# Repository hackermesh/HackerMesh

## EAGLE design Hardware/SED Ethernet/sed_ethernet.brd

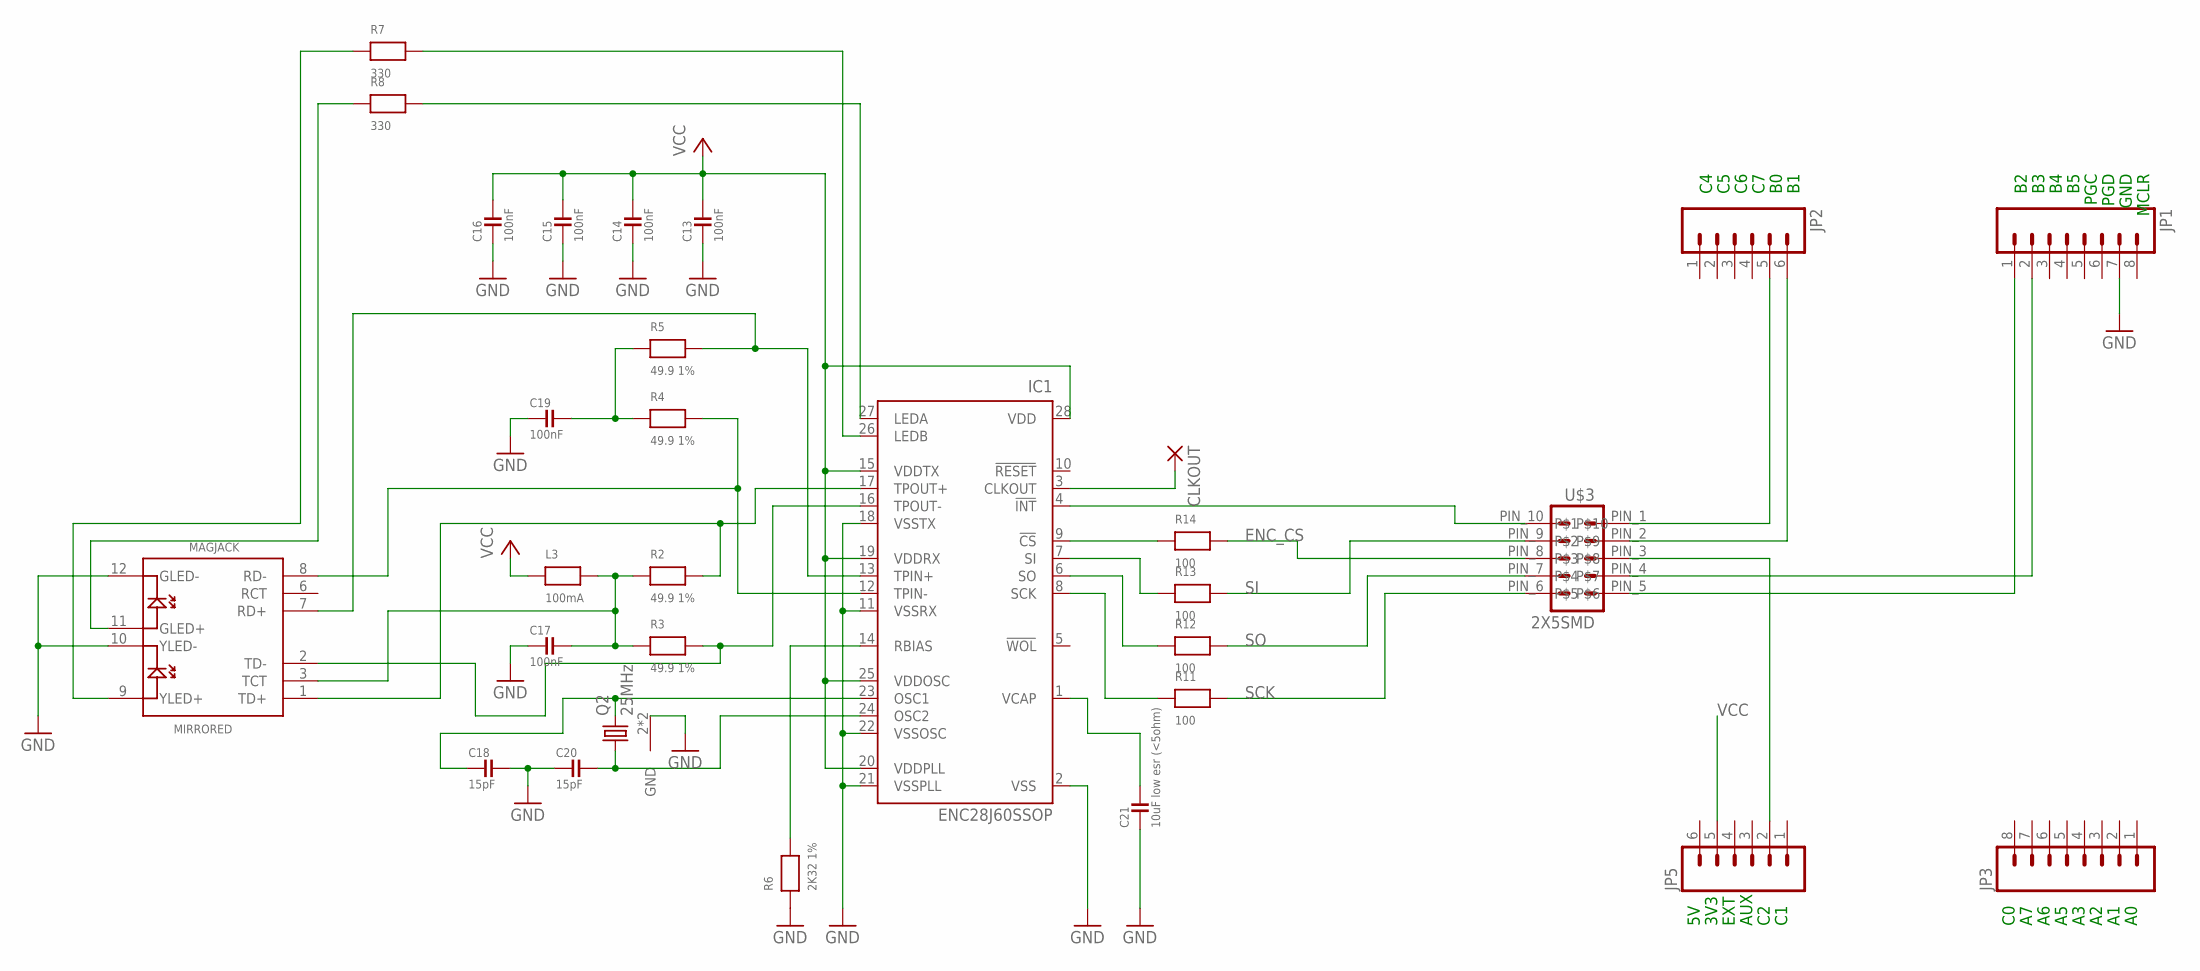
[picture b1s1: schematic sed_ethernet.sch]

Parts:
C13, C14, C15, C16, C17, C19: 100nF; 0805
C18, C20: 15pF; 0805
C21: 10uF low esr (<5ohm); 0805
CLKOUT: SMD2; SMD1,27-2,54
IC1: ENC28J60SSOP; SSOP28
JP1, JP3: M08; 1X08
JP2, JP5: M06SIP; 1X06
L3: 100mA; 0805
MIRRORED: MAGJACK
Q2: 25MHz; CRYSTAL-SMD-5X3
R2, R3, R4, R5: 49.9 1%; 0805
R6: 2K32 1%; 0805
R7, R8: 330; 0805
R11, R12, R13, R14: 100; 0805
U$3: 2X5SMD

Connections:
ENC_CS: R14.P$4 (2), U$3.PIN_8
GND: C13.P$3 (1), C14.P$3 (1), C15.P$3 (1), C16.P$3 (1), C17.P$3 (1), C18.P$4 (2), C19.P$3 (1), C20.P$3 (1), C21.P$3 (1), IC1.2 (VSS), IC1.11 (VSSRX), IC1.18 (VSSTX), IC1.21 (VSSPLL), IC1.22 (VSSOSC), JP1.7, MIRRORED.10 (YLED-), MIRRORED.12 (GLED-), Q2.2 (GND), Q2.4 (GND), R6.P$3 (1)
unnamed: IC1.14 (RBIAS), R6.P$4 (2)
unnamed: IC1.8 (SCK), R11.P$3 (1)
unnamed: IC1.6 (SO), R12.P$3 (1)
unnamed: IC1.7 (SI), R13.P$3 (1)
unnamed: IC1.9 (!CS), R14.P$3 (1)
unnamed: C21.P$4 (2), IC1.1 (VCAP)
unnamed: IC1.27 (LEDA), R8.P$4 (2)
unnamed: MIRRORED.11 (GLED+), R8.P$3 (1)
unnamed: MIRRORED.9 (YLED+), R7.P$3 (1)
unnamed: IC1.26 (LEDB), R7.P$4 (2)
unnamed: CLKOUT.1, IC1.3 (CLKOUT)
unnamed: IC1.17 (TPOUT+), MIRRORED.1 (TD+), R2.P$4 (2)
unnamed: IC1.16 (TPOUT-), MIRRORED.2 (TD-), R3.P$4 (2)
unnamed: C17.P$4 (2), L3.P$4 (2), MIRRORED.3 (TCT), R2.P$3 (1), R3.P$3 (1)
unnamed: IC1.13 (TPIN+), MIRRORED.7 (RD+), R5.P$4 (2)
unnamed: IC1.12 (TPIN-), MIRRORED.8 (RD-), R4.P$4 (2)
unnamed: C19.P$4 (2), R4.P$3 (1), R5.P$3 (1)
unnamed: C18.P$3 (1), IC1.23 (OSC1), Q2.3 (2)
unnamed: C20.P$4 (2), IC1.24 (OSC2), Q2.1
unnamed: JP2.5, U$3.PIN_1
unnamed: IC1.4 (!INT), U$3.PIN_10
unnamed: JP5.2, U$3.PIN_3
unnamed: JP2.6, U$3.PIN_2
unnamed: JP1.2, U$3.PIN_4
unnamed: JP1.1, U$3.PIN_5
SCK: R11.P$4 (2), U$3.PIN_6
SI: R13.P$4 (2), U$3.PIN_9
SO: R12.P$4 (2), U$3.PIN_7
VCC: C13.P$4 (2), C14.P$4 (2), C15.P$4 (2), C16.P$4 (2), IC1.15 (VDDTX), IC1.19 (VDDRX), IC1.20 (VDDPLL), IC1.25 (VDDOSC), IC1.28 (VDD), JP5.5, L3.P$3 (1)

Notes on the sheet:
3V3
EXT
AUX
PGC
PGD
GND
MCLR

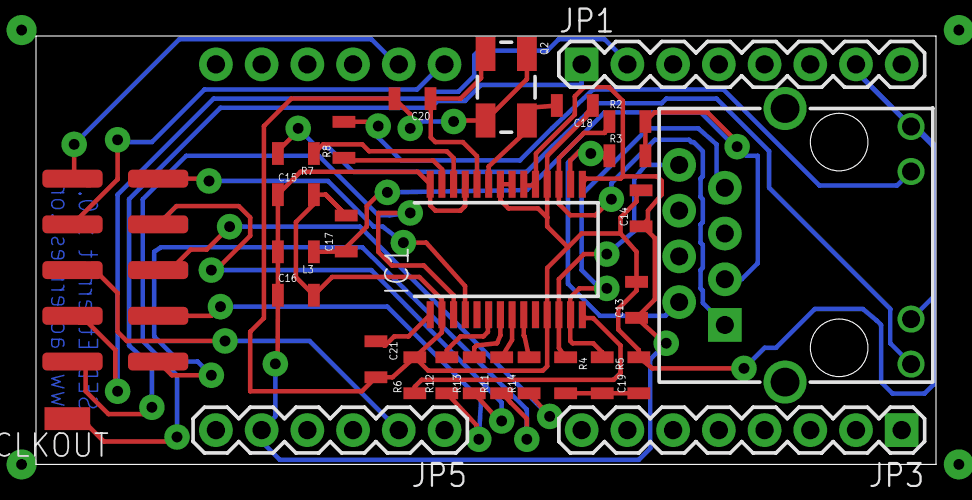
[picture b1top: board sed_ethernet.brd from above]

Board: 2 copper layers, 50.0 x 23.8 mm, 30 parts (1 on the bottom side), 31 nets.

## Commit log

2012-12-05 Estructura inicial
2012-12-05 Cristal con toma de tierra
